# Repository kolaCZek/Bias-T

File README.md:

# Bias-T

[OSHPark Project](https://oshpark.com/shared_projects/qdVj57Nw)

## BOM

 - 1x [1008 1800nH](https://www.tme.eu/en/details/cw1008-1800/smd-coils/ferrocore/)
 - 2x [0805 100pF](https://www.tme.eu/en/details/cc0805jrnpo9101/0805-mlcc-smd-capacitors/yageo/cc0805jrnpo9bn101/)
 - 2x [0805 1nF](https://www.tme.eu/en/details/cc0805jrnpo9102/0805-mlcc-smd-capacitors/yageo/cc0805jrnpo9bn102/)
 - 1x [0805 10nF](https://www.tme.eu/en/details/cc0805krx7r9103/0805-mlcc-smd-capacitors/yageo/cc0805krx7r9bb103/)
 - 1x [Micro USB](https://www.tme.eu/en/details/mx-47346-0001/usb-ieee1394-connectors/molex/473460001/)
 - 2x [SMA](https://www.ebay.com/sch/i.html?_from=R40&_sacat=0&_nkw=sma+female+pcb+edge+mount&rt=nc&LH_BIN=1)
 - 1x [PCB](https://oshpark.com/shared_projects/qdVj57Nw)

## Other Projects

 - [2m Band Pass Filter](https://github.com/kolaCZek/2m-Band-Pass-Filter)
 - [2m/70cm Diplexer](https://github.com/kolaCZek/2m-70cm-Diplexer)
 - [FM Trap](https://github.com/kolaCZek/FM-Trap)

## License

[Apache License Version 2.0](./LICENSE)

## Donate

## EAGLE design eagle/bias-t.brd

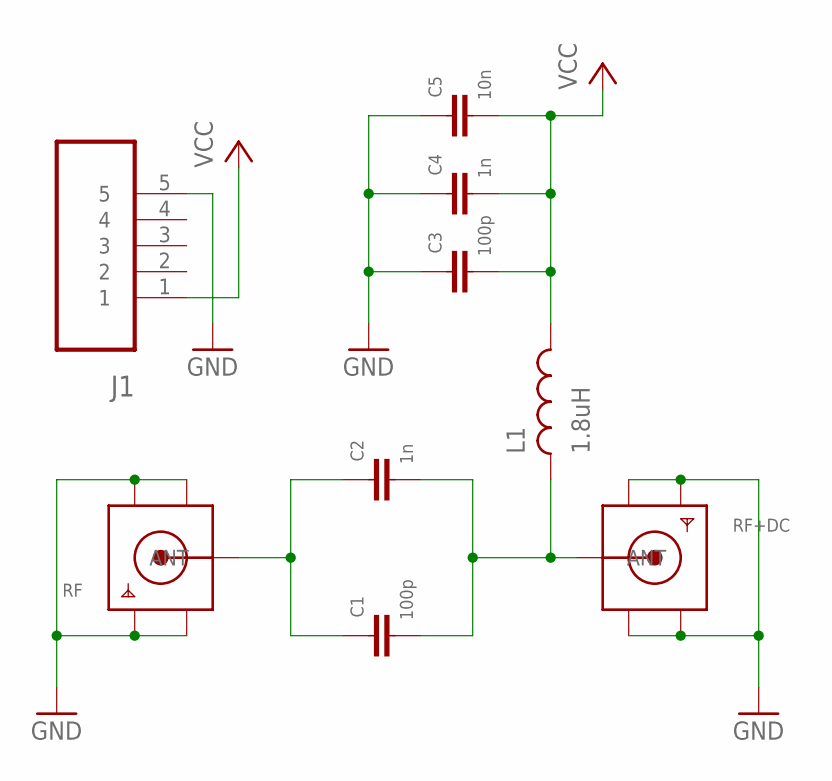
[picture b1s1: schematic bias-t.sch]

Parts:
C1, C3: 100p; 0805
C2, C4: 1n; 0805
C5: 10n; 0805
J1: 47346-0001; MOLEX_47346-0001
L1: 1.8uH; 1008INDUCTOR
RF: SMACONNECTOR_EDGE; SMA_EDGELAUNCH
RF+DC: SMACONNECTOR_EDGE; SMA_EDGELAUNCH

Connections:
GND: C3.P$2, C4.P$2, C5.P$2, J1.5, RF.GND@1 (GND4), RF.GND@2 (GND3), RF.GND@3 (GND2), RF.GND@4 (GND1), RF+DC.GND@1 (GND4), RF+DC.GND@2 (GND3), RF+DC.GND@3 (GND2), RF+DC.GND@4 (GND1)
unnamed: C1.P$2, C2.P$2, RF.P (ANT)
unnamed: C1.P$1, C2.P$1, L1.P$1, RF+DC.P (ANT)
VCC: C3.P$1, C4.P$1, C5.P$1, J1.1, L1.P$2

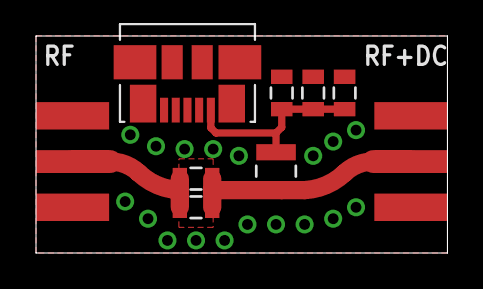
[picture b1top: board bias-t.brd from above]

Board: 2 copper layers, 22.9 x 12.1 mm, 9 parts (0 on the bottom side), 4 nets.

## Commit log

2018-02-15 init commit
2018-02-15 Image ling
2018-02-15 Readme - Other projects
2022-01-25 Add Buy me coffe button
